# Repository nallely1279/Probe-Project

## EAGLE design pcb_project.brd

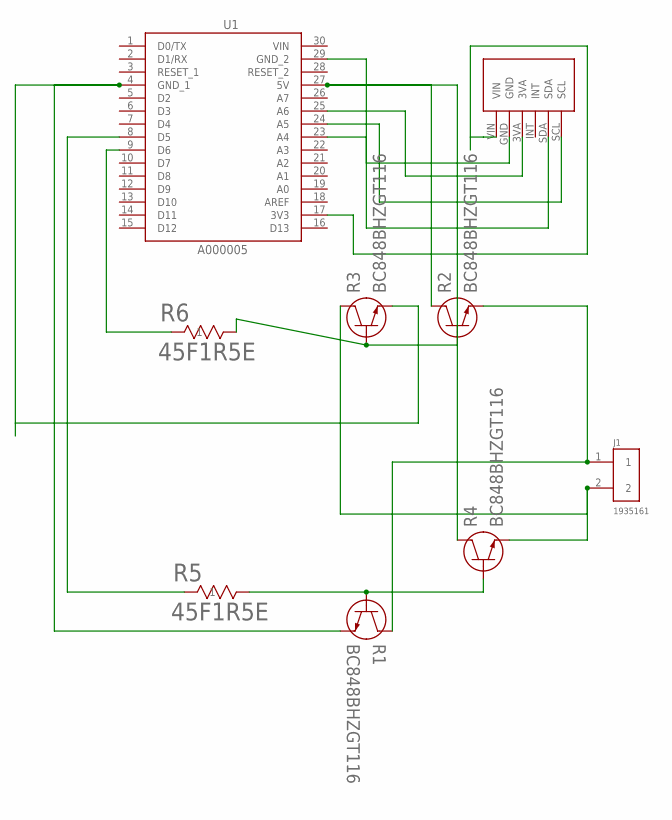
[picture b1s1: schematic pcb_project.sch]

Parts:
J1: 1935161; PHOENIX_1935161
R1, R2, R3, R4: BC848BHZGT116; TRANS_BC847BHZGT116_ROM
R5, R6: 45F1R5E; RES_45_OHM
U1: A000005; MODULE_A000005
U$1: TSL2591

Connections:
unnamed: U1.25 (A6), U$1.3VA
unnamed: R2.2 (11), R3.2 (11), R6.2
unnamed: U1.24 (A5), U$1.SCL
unnamed: U1.23 (A4), U$1.SDA
unnamed: U1.17 (3V3), U$1.VIN
unnamed: R1.2 (11), R4.2 (11), R5.2
unnamed: R6.1, U1.9 (D6)
unnamed: R5.1, U1.8 (D5)
unnamed: R2.1 (12), R4.1 (12), U1.27 (5V)
unnamed: R1.3 (13), R3.3 (13), U1.4 (GND_1)
unnamed: J1.1, R1.1 (12), R2.3 (13)
unnamed: J1.2, R3.1 (12), R4.3 (13)
unnamed: U1.29 (GND_2), U$1.GND
VIN: U1.30 (VIN)

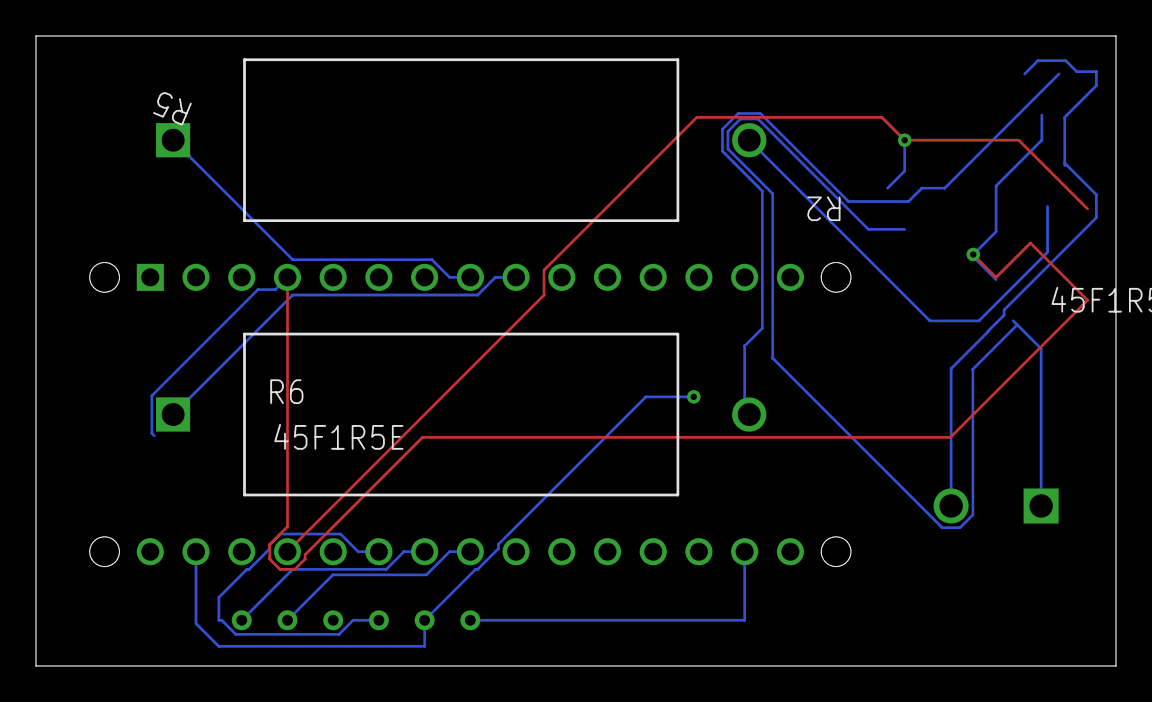
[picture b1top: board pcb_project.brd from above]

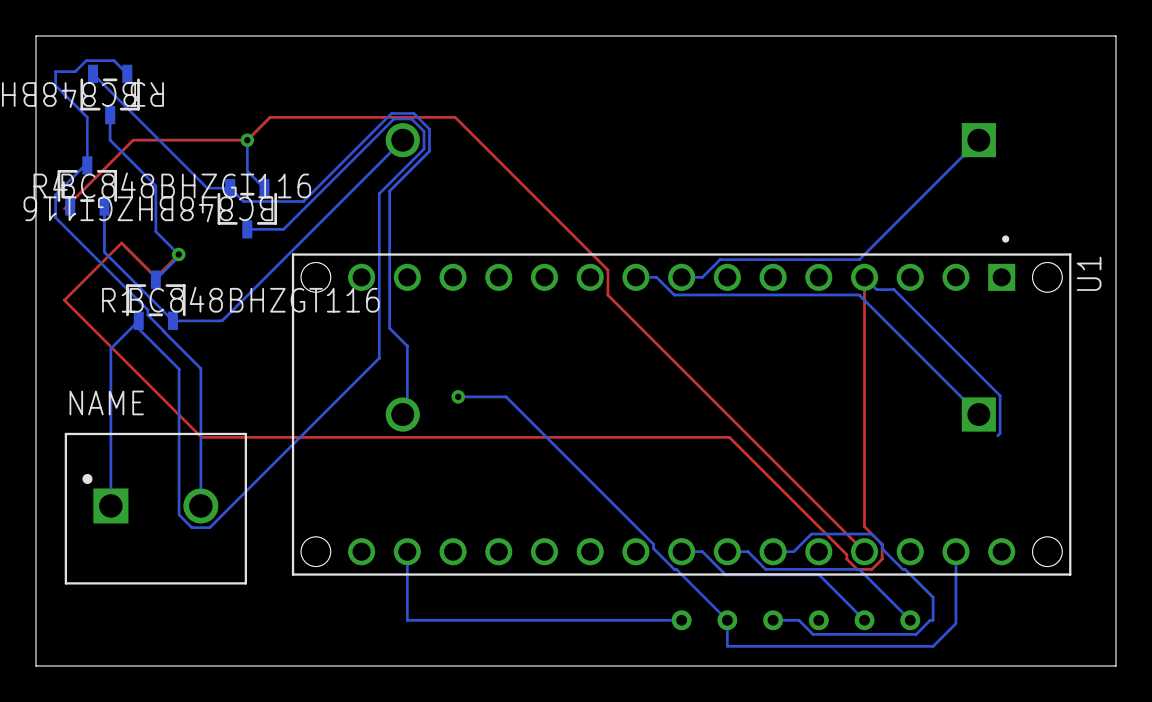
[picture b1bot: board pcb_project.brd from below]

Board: 2 copper layers, 60.0 x 35.0 mm, 9 parts (7 on the bottom side), 13 nets.

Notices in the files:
parts and their libraries:
COPYRIGHT: Copyright (C) 2018 Accelerated Designs. All rights reserved
